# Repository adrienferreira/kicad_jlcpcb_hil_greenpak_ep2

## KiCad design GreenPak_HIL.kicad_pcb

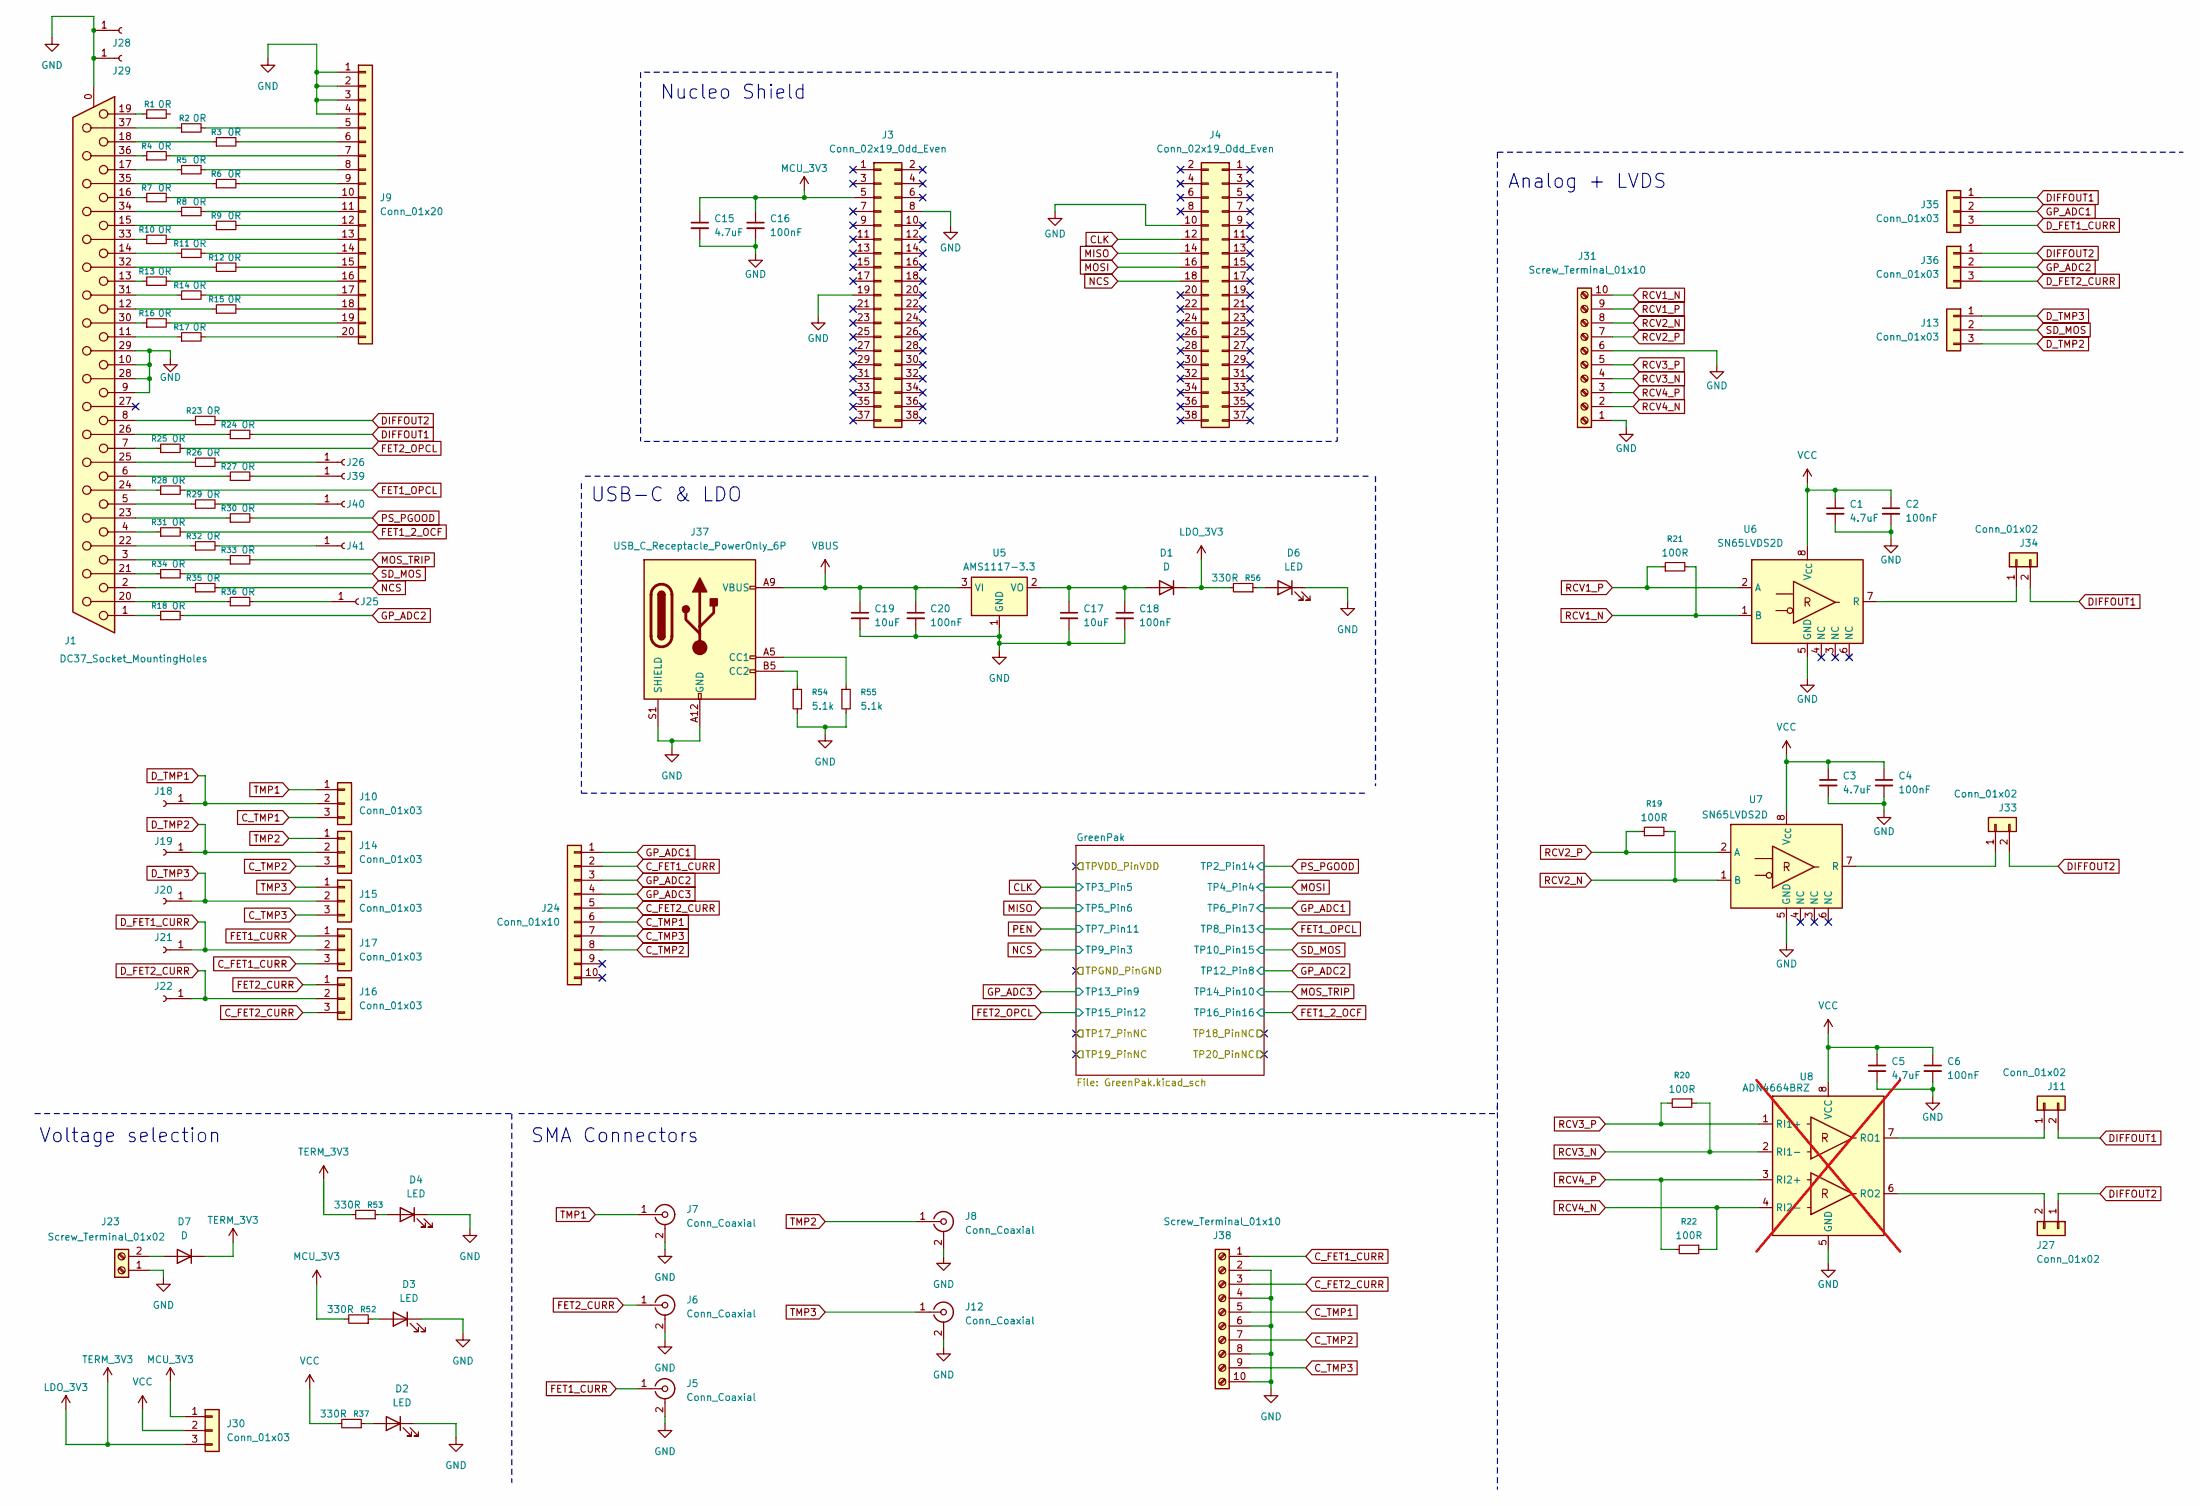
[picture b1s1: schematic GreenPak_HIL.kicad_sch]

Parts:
C1, C3, C5, C15: 4.7uF; C_0402_1005Metric; JLCPCB Part# C23733
C2, C4, C6, C16, C18, C20: 100nF; C_0402_1005Metric; JLCPCB Part# C1525
C17, C19: 10uF; C_0402_1005Metric; JLCPCB Part# C15525
D1, D7: D; D_SOD-323; JLCPCB Part# C191023
D2, D3, D4, D6: LED; LED_0805_2012Metric; JLCPCB Part# C25170728
J1: DC37_Socket_MountingHoles; DSUB-37_Socket_Vertical_P2.77x2.84mm_MountingHoles; JLCPCB Part# C7464456
J3, J4: Conn_02x19_Odd_Even; PinSocket_2x19_P2.54mm_Vertical; JLCPCB Part# C42372543
J5, J6, J7, J8, J12: Conn_Coaxial; BNC_Amphenol_B6252HB-NPP3G-50_Horizontal; JLCPCB Part# C2837588
J9: Conn_01x20; PinHeader_1x20_P2.54mm_Vertical; JLCPCB Part# C50981
J10, J13, J14, J15, J16, J17, J30, J35, J36: Conn_01x03; PinHeader_1x03_P2.54mm_Vertical; JLCPCB Part# C49257
J11, J27, J33, J34: Conn_01x02; PinHeader_1x02_P2.54mm_Vertical; JLCPCB Part# C492401
J18, J19, J20, J21, J22, J25, J26, J28, J29, J39, J40, J41: Conn_01x01_Socket; SolderWirePad_1x01_SMD_1x2mm; JLCPCB Part# C5199798
J23: Screw_Terminal_01x02; TerminalBlock_Xinya_XY308-2.54-2P_1x02_P2.54mm_Horizontal; JLCPCB Part# C42377752
J24: Conn_01x10; PinHeader_1x10_P2.54mm_Vertical; JLCPCB Part# C57369
J31: Screw_Terminal_01x10; TerminalBlock_Xinya_XY308-2.54-10P_1x10_P2.54mm_Horizontal; JLCPCB Part# C5188450
J37: USB_C_Receptacle_PowerOnly_6P; USB_C_Receptacle_GCT_USB4125-xx-x_6P_TopMnt_Horizontal; JLCPCB Part# C3151650
J38: Screw_Terminal_01x10; TerminalBlock_Xinya_XY308-2.54-10P_1x10_P2.54mm_Horizontal; JLCPCB Part # C5188450
R1, R2, R3, R4, R5, R6, R7, R8, R9, R10, R11, R12, R13, R14, R15, R16, R17, R18, R23, R24, R25, R26, R27, R28, R29, R30, R31, R32, R33, R34, R35, R36: 0R; R_0603_1608Metric; JLCPCB Part# C21189
R19, R20, R21, R22: 100R; R_0603_1608Metric; JLCPCB Part# C22775
R37, R52, R53, R56: 330R; R_0603_1608Metric; JLCPCB Part# C23138
R54, R55: 5.1k; R_0603_1608Metric; JLCPCB Part# C23186
U5: AMS1117-3.3; SOT-223-3_TabPin2; JLCPCB Part# C6186
U6, U7: SN65LVDS2D; SOIC-8_3.9x4.9mm_P1.27mm; JLCPCB Part# C2675079
U8: ADN4664BRZ; SOIC-8_3.9x4.9mm_P1.27mm; JLCPCB Part# C658626; not fitted

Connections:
CLK: J4.12; also elsewhere on the board
C_FET1_CURR: J17.3, J24.2, J38.1
C_FET2_CURR: J16.3, J24.5, J38.3
C_TMP1: J10.3, J24.6, J38.5
C_TMP2: J14.3, J24.8, J38.7
C_TMP3: J15.3, J24.7, J38.9
DIFFOUT1: J11.2, J34.2, J35.1, R24.2
DIFFOUT2: J27.1, J33.2, J36.1, R23.2
D_FET1_CURR: J17.2, J21.1, J35.3
D_FET2_CURR: J16.2, J22.1, J36.3
D_TMP1: J10.2, J18.1
D_TMP2: J13.3, J14.2, J19.1
D_TMP3: J13.1, J15.2, J20.1
FET1_2_OCF: R31.2; also elsewhere on the board
FET1_CURR: J5.1 (In), J17.1
FET1_OPCL: R28.2; also elsewhere on the board
FET2_CURR: J6.1 (In), J16.1
FET2_OPCL: R25.2; also elsewhere on the board
GND: C1.2, C2.2, C3.2, C4.2, C5.2, C6.2, C15.2, C16.2, C17.2, C18.2, C19.2, C20.2, D2.1 (K), D3.1 (K), D4.1 (K), D6.1 (K), J1.0 (PAD), J1.9, J1.10, J1.28, J1.29, J3.8, J3.19, J4.10, J5.2 (Ext), J6.2 (Ext), J7.2 (Ext), J8.2 (Ext), J9.1, J9.2, J9.3, J9.4, J12.2 (Ext), J23.1, J28.1, J29.1, J31.1, J31.6, J37.A12 (GND), J37.B12 (GND), J37.S1 (SHIELD), J38.2, J38.4, J38.6, J38.8, J38.10, R54.2, R55.2, U5.1 (GND), U6.5 (GND), U7.5 (GND), U8.5 (GND); also elsewhere on the board
GP_ADC1: J24.1, J35.2; also elsewhere on the board
GP_ADC2: J24.3, J36.2, R18.2; also elsewhere on the board
GP_ADC3: J24.4; also elsewhere on the board
LDO_3V3: D1.1 (K), D7.1 (K), J30.3, R53.2, R56.2
MCU_3V3: C15.1, C16.1, J3.5, J30.1, R52.2
MISO: J4.14; also elsewhere on the board
MOSI: J4.16; also elsewhere on the board
MOS_TRIP: R33.2; also elsewhere on the board
NCS: J4.18, R35.2; also elsewhere on the board
unnamed: C17.1, C18.1, D1.2 (A), U5.2 (VO)
unnamed: D2.2 (A), R37.1
unnamed: D3.2 (A), R52.1
unnamed: D4.2 (A), R53.1
unnamed: D6.2 (A), R56.1
unnamed: D7.2 (A), J23.2
unnamed: J1.1, R18.1
unnamed: J1.2, R35.1
unnamed: J1.3, R33.1
unnamed: J1.4, R31.1
unnamed: J1.5, R29.1
unnamed: J1.6, R27.1
unnamed: J1.7, R25.1
unnamed: J1.8, R23.1
unnamed: J1.11, R17.1
unnamed: J1.12, R15.1
unnamed: J1.13, R13.1
unnamed: J1.14, R11.1
unnamed: J1.15, R9.1
unnamed: J1.16, R7.1
unnamed: J1.17, R5.1
unnamed: J1.18, R3.1
unnamed: J1.19, R1.1
unnamed: J1.20, R36.1
unnamed: J1.21, R34.1
unnamed: J1.22, R32.1
unnamed: J1.23, R30.1
unnamed: J1.24, R28.1
unnamed: J1.25, R26.1
unnamed: J1.26, R24.1
unnamed: J1.30, R16.1
unnamed: J1.31, R14.1
unnamed: J1.32, R12.1
unnamed: J1.33, R10.1
unnamed: J1.34, R8.1
unnamed: J1.35, R6.1
unnamed: J1.36, R4.1
unnamed: J1.37, R2.1
unnamed: J9.5, R2.2
unnamed: J9.6, R3.2
unnamed: J9.7, R4.2
unnamed: J9.8, R5.2
unnamed: J9.9, R6.2
unnamed: J9.10, R7.2
unnamed: J9.11, R8.2
unnamed: J9.12, R9.2
unnamed: J9.13, R10.2
unnamed: J9.14, R11.2
unnamed: J9.15, R12.2
unnamed: J9.16, R13.2
unnamed: J9.17, R14.2
unnamed: J9.18, R15.2
unnamed: J9.19, R16.2
unnamed: J9.20, R17.2
unnamed: J11.1, U8.7 (RO1)
unnamed: J25.1, R36.2
unnamed: J26.1, R26.2
unnamed: J27.2, U8.6 (RO2)
unnamed: J33.1, U7.7 (R)
unnamed: J34.1, U6.7 (R)
unnamed: J37.A5 (CC1), R55.1
unnamed: J37.B5 (CC2), R54.1
unnamed: J39.1, R27.2
unnamed: J40.1, R29.2
unnamed: J41.1, R32.2
PS_PGOOD: R30.2; also elsewhere on the board
RCV1_N: J31.10, R21.2, U6.1 (B)
RCV1_P: J31.9, R21.1, U6.2 (A)
RCV2_N: J31.8, R19.2, U7.1 (B)
RCV2_P: J31.7, R19.1, U7.2 (A)
RCV3_N: J31.4, R20.1, U8.2 (RI1-)
RCV3_P: J31.5, R20.2, U8.1 (RI1+)
RCV4_N: J31.2, R22.1, U8.4 (RI2-)
RCV4_P: J31.3, R22.2, U8.3 (RI2+)
SD_MOS: J13.2, R34.2; also elsewhere on the board
TMP1: J7.1 (In), J10.1
TMP2: J8.1 (In), J14.1
TMP3: J12.1 (In), J15.1
VBUS: C19.1, C20.1, J37.A9 (VBUS), J37.B9 (VBUS), U5.3 (VI); also elsewhere on the board
VCC: C1.1, C2.1, C3.1, C4.1, C5.1, C6.1, J30.2, R37.2, U6.8 (V_{CC}), U7.8 (V_{CC}), U8.8 (VCC); also elsewhere on the board

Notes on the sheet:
Voltage selection
Analog + LVDS
USB-C & LDO
SMA Connectors
Nucleo Shield

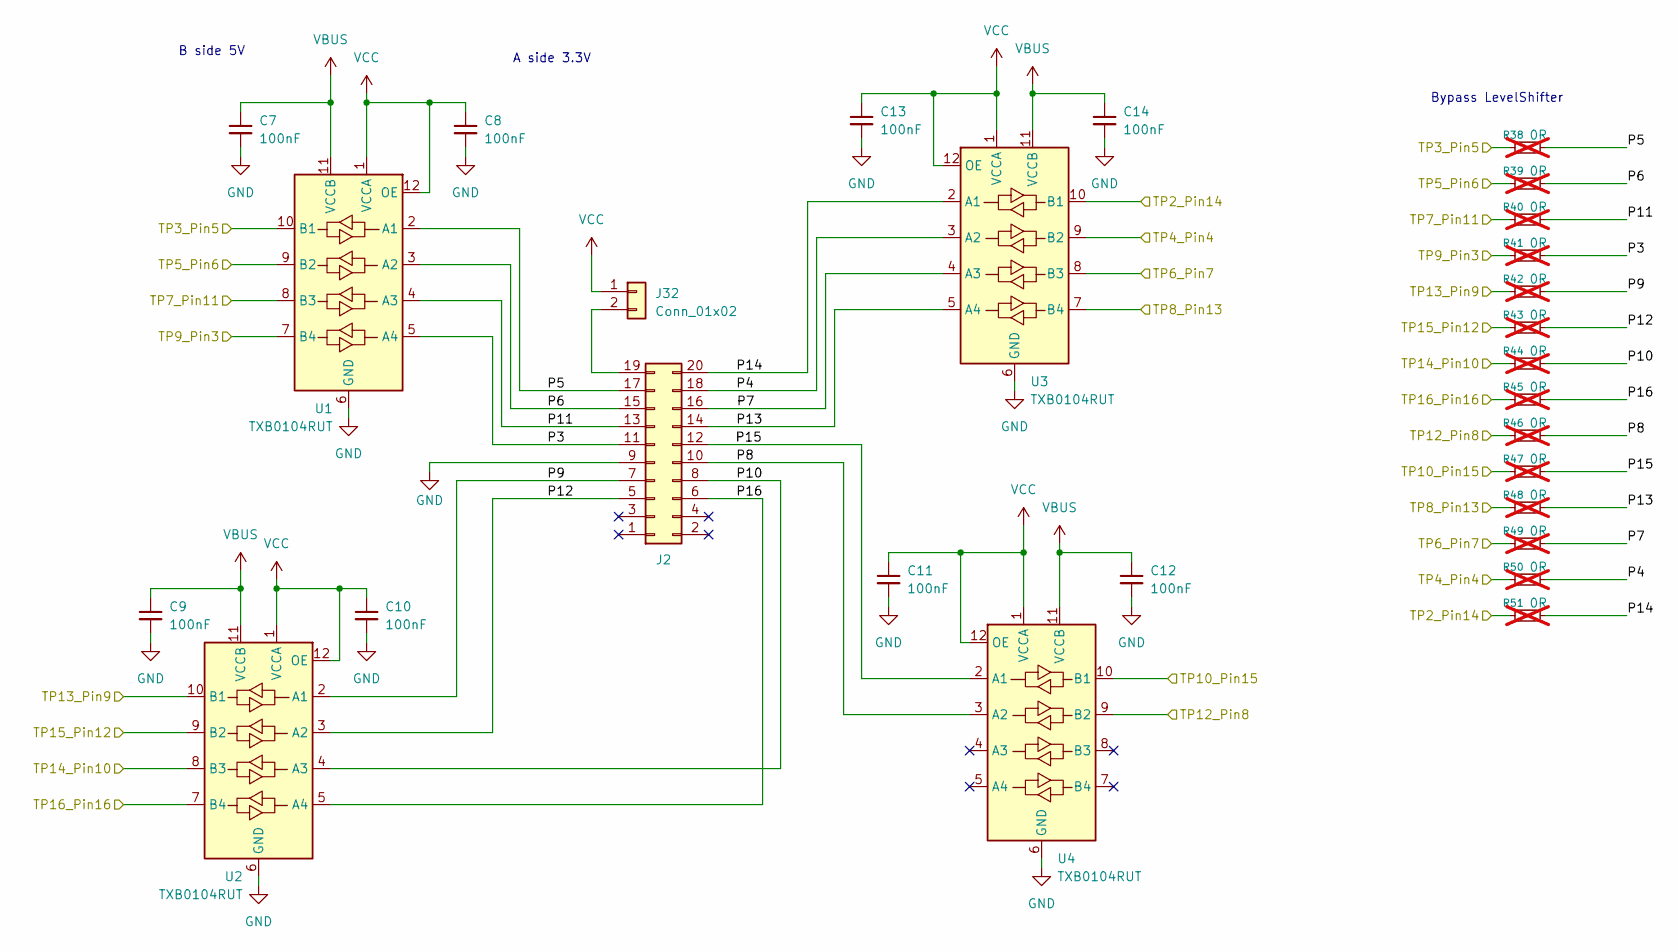
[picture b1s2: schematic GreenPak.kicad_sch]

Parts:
C7, C8, C9, C10, C11, C12, C13, C14: 100nF; C_0402_1005Metric; JLCPCB Part# C1525
J2: Conn_02x10_Odd_Even; PinHeader_2x10_P2.54mm_Vertical; JLCPCB Part# C706900
J32: Conn_01x02; PinHeader_1x02_P2.54mm_Vertical; JLCPCB Part# C492401
R38, R39, R40, R41, R42, R43, R44, R45, R46, R47, R48, R49, R50, R51: 0R; R_0603_1608Metric; JLCPCB Part# C21189; not fitted
U1, U2, U3, U4: TXB0104RUT; Texas_R-PUQFN-N12; JLCPCB Part# C105266

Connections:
/GreenPak/P3: J2.11, R41.2, U1.5 (A4)
/GreenPak/P4: J2.18, R50.2, U3.3 (A2)
/GreenPak/P5: J2.17, R38.2, U1.2 (A1)
/GreenPak/P6: J2.15, R39.2, U1.3 (A2)
/GreenPak/P7: J2.16, R49.2, U3.4 (A3)
/GreenPak/P8: J2.10, R46.2, U4.3 (A2)
/GreenPak/P9: J2.7, R42.2, U2.2 (A1)
/GreenPak/P10: J2.8, R44.2, U2.4 (A3)
/GreenPak/P11: J2.13, R40.2, U1.4 (A3)
/GreenPak/P12: J2.5, R43.2, U2.3 (A2)
/GreenPak/P13: J2.14, R48.2, U3.5 (A4)
/GreenPak/P14: J2.20, R51.2, U3.2 (A1)
/GreenPak/P15: J2.12, R47.2, U4.2 (A1)
/GreenPak/P16: J2.6, R45.2, U2.5 (A4)
CLK: R38.1, U1.10 (B1); also elsewhere on the board
FET1_2_OCF: R45.1, U2.7 (B4); also elsewhere on the board
FET1_OPCL: R48.1, U3.7 (B4); also elsewhere on the board
FET2_OPCL: R43.1, U2.9 (B2); also elsewhere on the board
GND: C7.2, C8.2, C9.2, C10.2, C11.2, C12.2, C13.2, C14.2, J2.9, U1.6 (GND), U2.6 (GND), U3.6 (GND), U4.6 (GND); also elsewhere on the board
GP_ADC1: R49.1, U3.8 (B3); also elsewhere on the board
GP_ADC2: R46.1, U4.9 (B2); also elsewhere on the board
GP_ADC3: R42.1, U2.10 (B1); also elsewhere on the board
MISO: R39.1, U1.9 (B2); also elsewhere on the board
MOSI: R50.1, U3.9 (B2); also elsewhere on the board
MOS_TRIP: R44.1, U2.8 (B3); also elsewhere on the board
NCS: R41.1, U1.7 (B4); also elsewhere on the board
unnamed: J2.19, J32.2
PEN: R40.1, U1.8 (B3)
PS_PGOOD: R51.1, U3.10 (B1); also elsewhere on the board
SD_MOS: R47.1, U4.10 (B1); also elsewhere on the board
VBUS: C7.1, C9.1, C12.1, C14.1, U1.11 (VCCB), U2.11 (VCCB), U3.11 (VCCB), U4.11 (VCCB); also elsewhere on the board
VCC: C8.1, C10.1, C11.1, C13.1, J32.1, U1.1 (VCCA), U1.12 (OE), U2.1 (VCCA), U2.12 (OE), U3.1 (VCCA), U3.12 (OE), U4.1 (VCCA), U4.12 (OE); also elsewhere on the board

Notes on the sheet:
Bypass LevelShifter
A side 3.3V
B side 5V

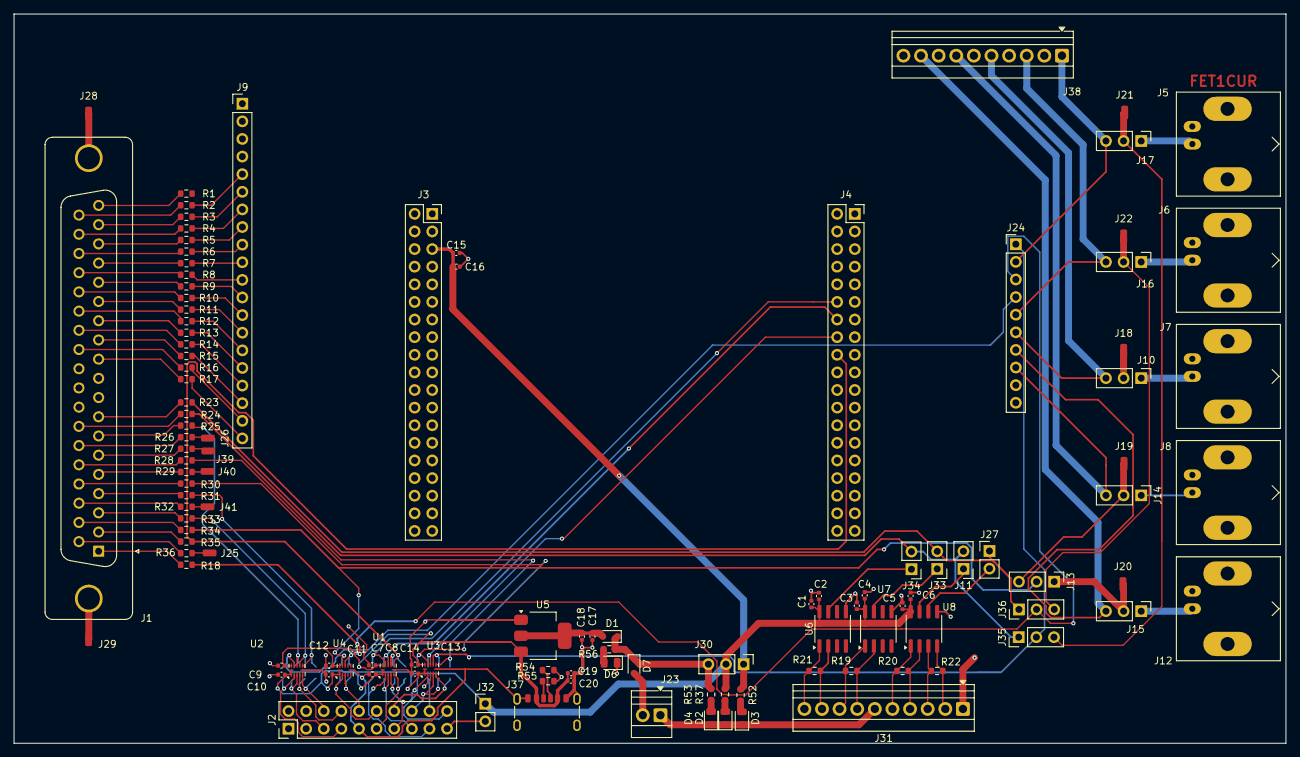
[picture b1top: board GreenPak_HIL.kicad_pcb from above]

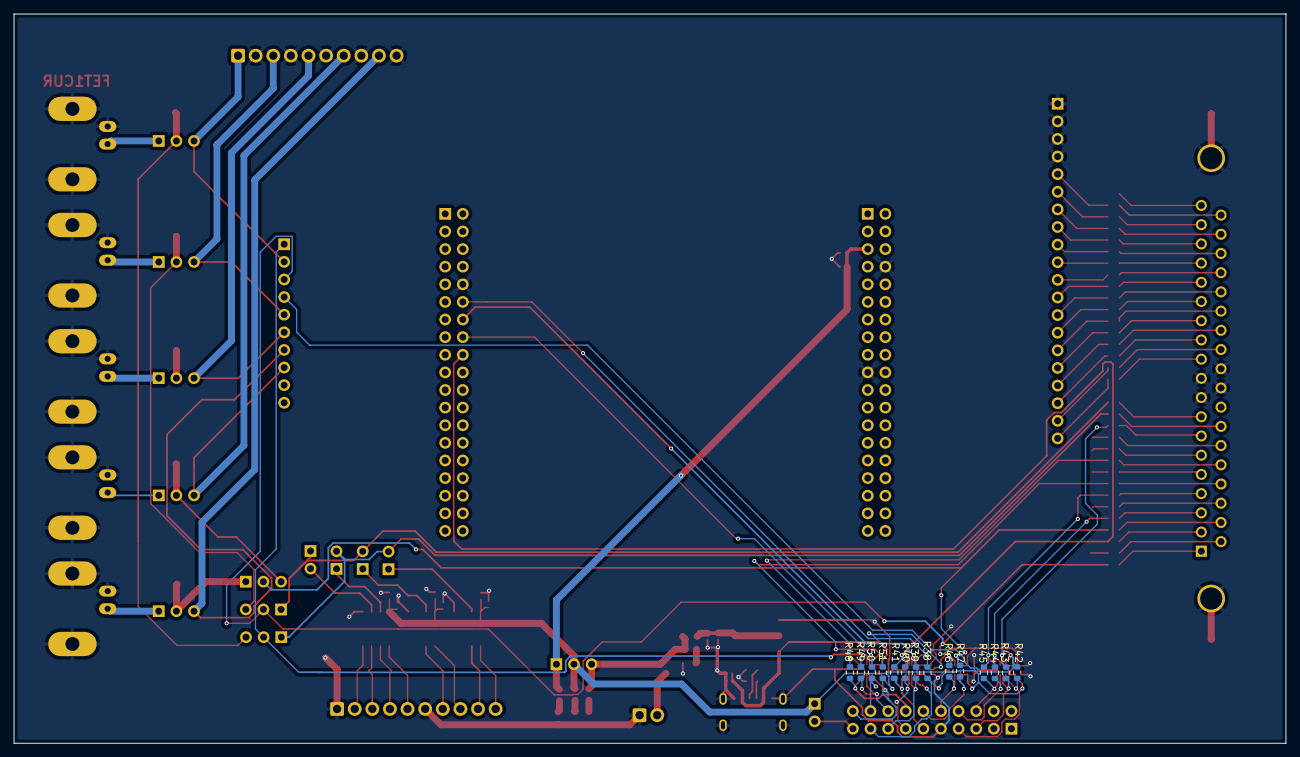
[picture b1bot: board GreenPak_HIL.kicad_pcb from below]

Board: 2 copper layers, 183.4 x 105.2 mm, 131 parts (14 on the bottom side), 124 nets.
